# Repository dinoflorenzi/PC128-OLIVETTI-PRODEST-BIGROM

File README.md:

# PC128-OLIVETTI-PRODEST-BIGROM
## PROJECT OVERVIEW
Questo è un progetto nato per realizzare una cartuccia rom multi pagina per il mio PC 128 OLIVETTI PRODEST HOME COMPUTER.
Ho progettato e costruito due diverse schede ROM basate su due diversi chip ROM.
Una scheda ROM è basata sul chip rom at28c256, la seconda è basata sul chip flash sst39f040.
Inoltre ho codificato le routine ASM 6809 per gestirle.<br/>

## COME E' NATO IL PROGETTO
Molte sono le cartucce rom progettate, ma ho avuto la necessità di progettare la mia versione, con pochi semplici componenti e la possibilità di programmare la rom dal pc128 stesso, senza utilizzare strumenti di programmazione esterni.
Infatti, è possibile caricare l'immagine rom da masterizzare, utilizzando un dispositivo a cassetta o tramite connessione seriale a un PC esterno.<br/>
## PORTA PER CARTUCCE
I computer PC128 dispongono di una porta per cartucce con i segnali principali del computer, bus dati a 8 bit, bus indirizzi a 16 bit, chip select, master clock.<br/>
<br/>
## SCELTA DELLE ROM CHIP
La prima selezione di chip AT28C256 si basa sulla sua architettura semplice, bus a 8 bit, indirizzo a 15 bit ed è molto semplice da programmare. Un altro buon motivo è che avevo 3 componenti di riserva nel mio cassetto :)
La selezione del secondo chip SST39F040 si basa anche sul suo package (DIP32), sulla tecnologia pth, sul bus a 8 bit, e soprattutto sulla sua dimensione di 512 kbyte che permette di commutare tra 32 pagine da 16 kbyte ciascuna.
Gli sviluppi della scheda singola sono meglio descritti nei link sottostanti o nella sezione wiki<br/>

[CARTUCCIA A PAGINA SINGOLA](https://github.com/dinoflorenzi/PC128-OLIVETTI-PRODEST-BIGROM/wiki/Single-Page-Rom)<br/>

[BIGROM](https://github.com/dinoflorenzi/PC128-OLIVETTI-PRODEST-BIGROM/wiki/BigRom)<br/>

### INSTALLAZIONE DELLA BIGROM
La cartuccia si installa nello sportellino centrale del PC128, a computer spento, come mostrato nella foto<br/>
Per l' installazione del software di gestione della bigrom è possibile utilizzare un programmatore utilizzando il file bigrom.eeprom, in tal caso la flash deve essere programmata prima dell' installazione sulla scheda. Altrimenti è possibile caricare il programma di gestione da registratore utilizzando un'audiocassetta su cui deve essere registrato il file audio bigrom.k7.wav. Dopodiché da basic 128 digitare<br/>
CLEAR,&H2FFF<br/>
LOADM"CASS:",,R<br/>
A questo punto sarà possibile caricare il file bigrom.rom in posizione V che è la posizione di boo.</br>
<br/>

### FILE MANAGER DELLA BIGROM
Una delle 32 pagine della Bigrom è dedicata al programma di gestione della Bigrom stessa.
La schermata principale visualizza l'elenco dei programmi contenuti nella Bigrom. Basta premere il relativo tasto per scegliere la ROM.
Una volta avviata la ROM per tornare al programma BIGROM bisogna spegnere e riaccendere il computer.<br/>
<br/>
Premendo il tasto STOP dal menu di scelta delle ROMS si entra nel menu di gestione della ROM.<br/>
<br/>

### CONNESSIONE SERIALE
La connessione seriale sfrutta un UART-USB adapter, che connette il PC128 ad un computer con sistema opperativo windows.
Per il funzionamento del cavo seriale sarà necessario installare i [drivers](https://github.com/dinoflorenzi/PC128-OLIVETTI-PRODEST-BIGROM/tree/main/SERIAL-INTERFACE/Software/WIN_DRIVERS).<br/>E' consigliato l' utilizzo dell' interfaccia CH340 per un discorso di compatibilità.<br/>
Il [cavo](https://github.com/dinoflorenzi/PC128-OLIVETTI-PRODEST-BIGROM/wiki/Serial-Cable) si connette alla porta joystick 2 del PC128 e ad una qualsiasi porta USB del computer Windows.<br/>
<br/><br/>
Dal lato computer Windows si deve avviare il programma [VSerialRomT.exe](https://github.com/dinoflorenzi/PC128-OLIVETTI-PRODEST-BIGROM/blob/main/SERIAL-INTERFACE/Software/VSerialRomT.exe) con il quale si potranno selezionare le roms da caricare, nell'ordine in cui sono inserite, dopodichè premere LOAD. Il programma si mette in attesa del PC128.<br/>
Dal lato PC128 bisogna entrare nel menu di gestione premendo STOP, poi premere F per il caricamento multiplo e successivamente confermare la scelta .<br/> 
Attenzione se non si dispone dello spazio, verranno caricate solamente le ROMS negli spazi vuoti. L'alternativa è cancellare le ROMS non utilizzate.<br/>
#### ATTENZIONE!!!! la posizione del programma di gestione della BIGROM non deve essere cambiato.<br/>
<br/><br/>
<br/><br/>

## VIDEO DEMO
Below, a demostrating videos.<br/>

## SVILUPPI FUTURI 
Sincronizzazione del contenuto della Bigrom con il programma di caricamento e gestione drag&drop.
Incremento della velocità della seriale.
Esecuzione di programmi in basic.
## SOFTWARE TOOLS
[Kicad](https://www.kicad.org/) and [Freerounting](https://freerouting.org/) to develop schematics and pcb.<br/>
[CMOC](http://perso.b2b2c.ca/~sarrazip/dev/cmoc.html) C compiler to develop page 0 Rom Tool.

## DOVE TROVARE LE ROMS
https://github.com/dinoflorenzi/PC128-OLIVETTI-PRODEST-BIGROM/tree/main/ROMS
http://dcmoto.free.fr/programmes/_html/support_memo5.html
https://www.6502man.com/Bricolages/MEMO5_multirom/MEMO5_multirom.html
## RESOURCES
http://dcmoto.free.fr/documentation/schemas/mo6.png
https://www.mouser.it/datasheet/2/268/doc0006-1108095.pdf
https://www.mouser.it/datasheet/2/268/39%20Series_MPF_MPF__Product%20Brief-373259.pdf

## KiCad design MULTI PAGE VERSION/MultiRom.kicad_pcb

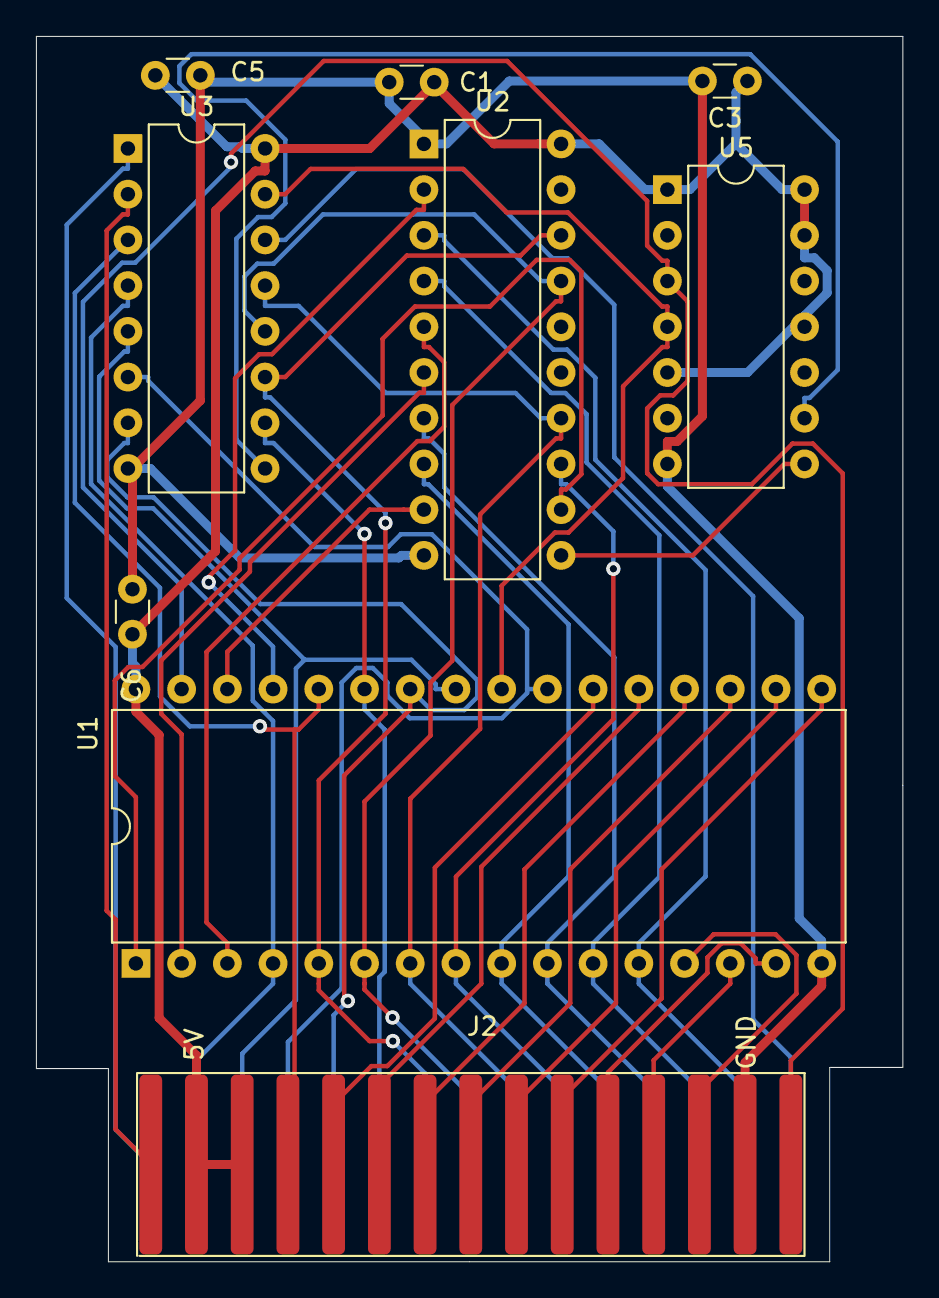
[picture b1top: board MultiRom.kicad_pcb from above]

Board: 2 copper layers, 48.1 x 68.1 mm, 10 parts (1 on the bottom side), 37 nets.

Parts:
C1, C3, C5, C6: 100nF; C_Disc_D3.0mm_W1.6mm_P2.50mm
J1, J2: Conn_01x15_Male; EdgeConn_15
U1: SST39SF040; DIP-32_W15.24mm
U2: 74LS373; DIP-20_W7.62mm
U3: 74LS133; DIP-16_W7.62mm
U5: 74LS04; DIP-14_W7.62mm

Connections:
+5V: C1.1, C3.1, C5.1, C6.1, J2.2, J2.3, U1.32, U2.20, U3.16, U5.1, U5.5, U5.11, U5.13, U5.14
A0: J1.14, U1.12, U2.3
A1: J1.13, U1.11, U2.4
A2: J1.12, U1.10, U2.7
A3: J1.11, U1.9, U2.8
A4: J1.10, U1.8, U2.13
A5: J1.9, U1.7, U2.14, U3.13
A6: J1.8, U1.6, U2.17, U3.12
A7: J1.7, U1.5, U2.18, U3.11
A8: J1.6, U1.27, U3.10
A9: J1.5, U1.26, U3.7
A10: J1.4, U1.23, U3.6
A11: J1.3, U1.25, U3.5
A12: J1.2, U1.4, U3.4
A13: J2.4, U1.28, U3.3
A14: J2.1, U3.2
A15: J1.1, U3.1
CS: J2.5, U1.22
D0: J2.13, U1.13
D1: J2.12, U1.14
D2: J2.11, U1.15
D3: J2.10, U1.17
D4: J2.9, U1.18
D5: J2.8, U1.19
D6: J2.7, U1.20
D7: J2.6, U1.21
E: J1.15, U3.14
GND: C1.2, C3.2, C5.2, C6.2, J2.14, U1.16, U2.1, U2.10, U3.8, U5.7
unnamed: U1.1, U2.12
unnamed: U1.2, U2.6
unnamed: U1.3, U2.5
unnamed: U1.29, U2.2
unnamed: U1.30, U2.9
unnamed: U2.11, U5.8
unnamed: U3.9, U5.9
OE: U1.24, U3.15, U5.4
RW: J2.15, U1.31, U5.3

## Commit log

2022-07-10 Modello 3D case
2022-07-16 fix modelli STL per stampa 3D - modificato logo - modificata svasatura viti
2022-08-12 Case rialzato a 24mm Aumentata altezza case e coperchio a 24mm Aumentato spessore parete dal lato del connettore Aggiunto rinforzo lato connettore Vecchio progetto Freecad spostato in cartella a part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
2022-08-14 Aggiornato modello 3D case (multipart)
2022-08-19 Fix logo troppo fragile per stampa 3D
2022-09-04 Allargato spessore griglie a 2mm Fix per rottura in fase di stampa 3D
2022-11-26 Bigrom MENU bin/src
2023-05-07 USB->UART_Cable Driver PL2303 Chipset
2023-05-07 USB->UART CH340 CHIPSET DRIVER
2024-10-19 Add files via upload
    - baudrate a 19200
    - incrementata velocità di scrittura flash
    - calcolo CRC rom
2024-10-29 Add files via upload
    versione a 32bit
2024-11-01 Add files via upload
    32bit version
2024-12-23 Add files via upload
    Seriale a 38400, scrittura cassette da K7
2024-12-28 Add files via upload
    +delay
